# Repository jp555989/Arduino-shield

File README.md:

# Arduino-shield
This is a project I made for my engineer thesis which involves designing a shield for Arduino with as many useful functions as possible, using ready to program modules like LCD Display, RTC module, etc.

I used KiCad for designing the PCB and LtSpice for the simulation of electronic circuits, simulations involved op-amp in voltage phase inverting configuration, buffer and resistor ladder with Monte Carlo Method.

Presented files have updated version of PCB with important fixes, the board presented on photos is the older version.

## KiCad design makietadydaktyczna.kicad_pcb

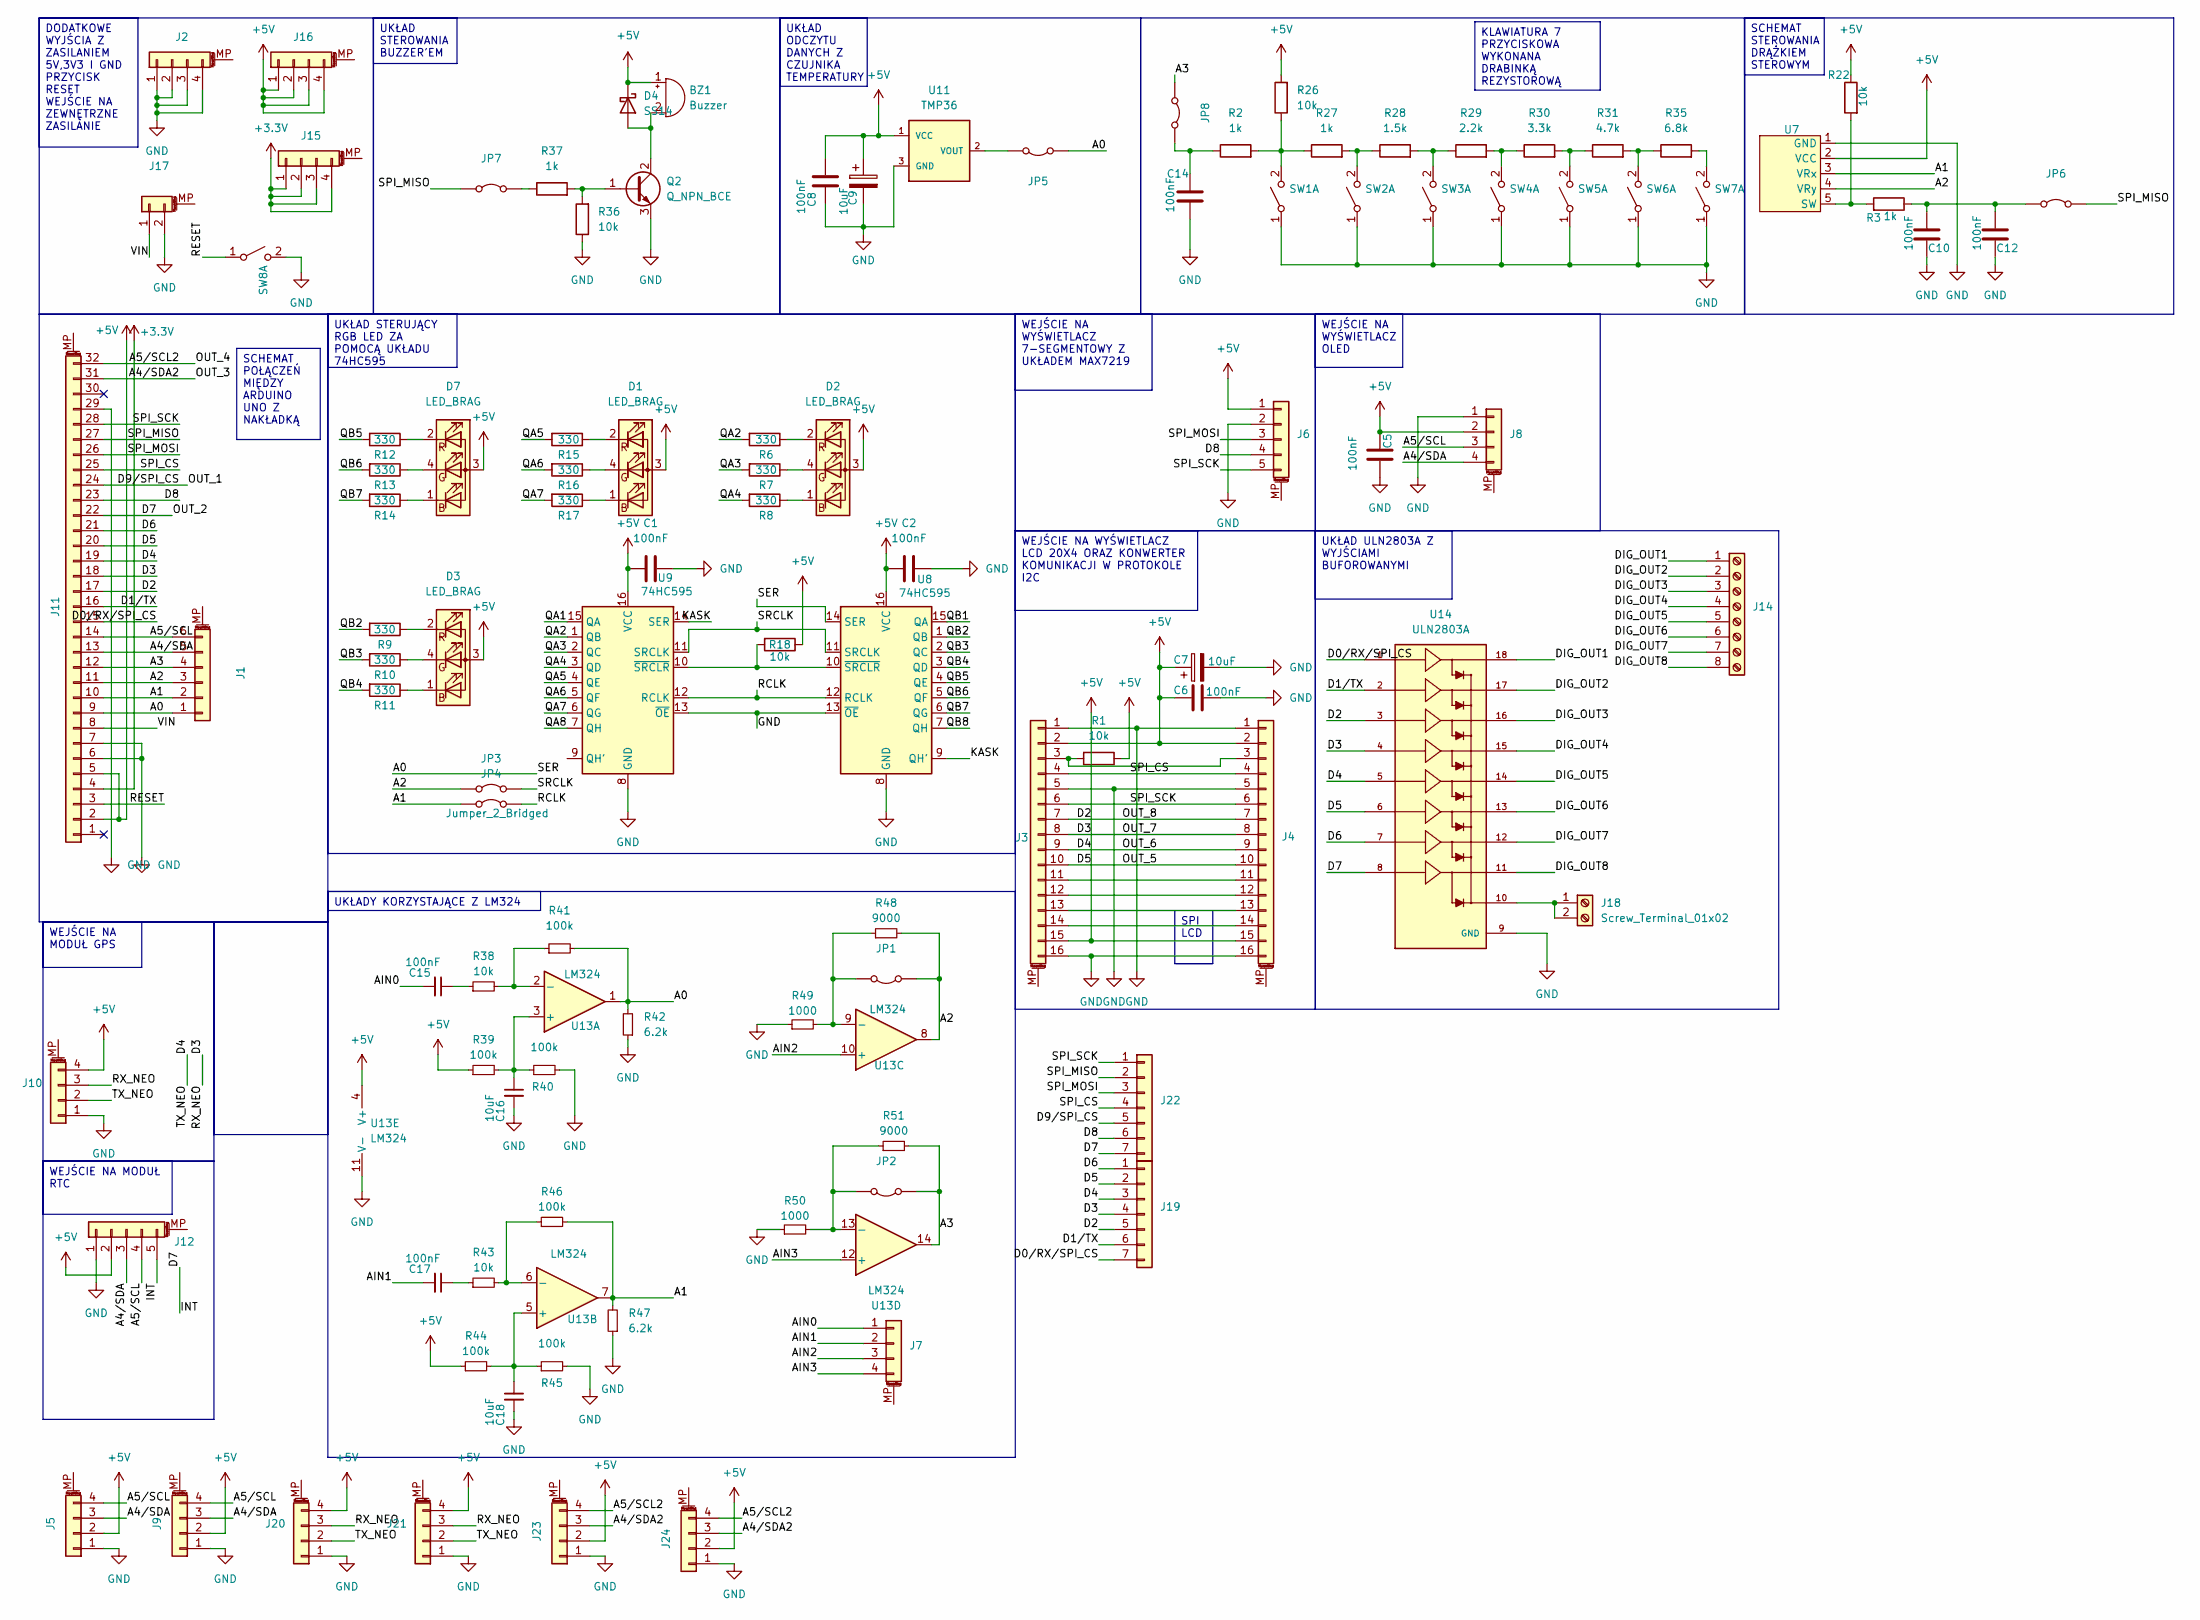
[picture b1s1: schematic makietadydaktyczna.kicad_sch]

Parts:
BZ1: Buzzer; Buzzer_D14mm_H7mm_P10mm
C1, C2, C5, C6, C8, C10, C12, C14, C15, C17: 100nF; C_0805_2012Metric_Pad1.18x1.45mm_HandSolder
C7, C9: 10uF; C_Radial_D5.0mm_H11.0mm_P2.00mm
C16, C18: 10uF; C_0805_2012Metric_Pad1.18x1.45mm_HandSolder
D1, D2, D3, D7: LED_BRAG; LED_D5.0mm-4_RGB_Wide_Pins
D4: SS14; D_SMA
J1: Conn_01x06_MountingPin; PinSocket_1x06_P2.54mm_Vertical
J2, J5, J8, J9, J10, J15, J16, J20, J21, J23, J24: Conn_01x04_MountingPin; PinSocket_1x04_P2.54mm_Vertical
J3, J4: Conn_01x16_MountingPin; PinSocket_1x16_P2.54mm_Vertical
J6, J12: Conn_01x05_MountingPin; PinSocket_1x05_P2.54mm_Vertical
J7: Conn_01x04_MountingPin; PinHeader_1x04_P2.54mm_Vertical
J11: Conn_01x32_MountingPin; Arduino_UNO_R3
J14: Screw_Terminal_01x08; TerminalBlock_Xinya_XY308-2.54-8P_1x08_P2.54mm_Horizontal
J17: Conn_01x02_MountingPin; PinSocket_1x02_P2.54mm_Vertical
J18: Screw_Terminal_01x02; TerminalBlock_Xinya_XY308-2.54-2P_1x02_P2.54mm_Horizontal
J19, J22: Conn_01x07; PinSocket_1x07_P2.54mm_Vertical
JP1, JP2, JP3, JP4, JP5, JP6, JP7, JP8: Jumper_2_Bridged; PinHeader_1x02_P2.54mm_Vertical
Q2: Q_NPN_BCE; TO-92
R1, R18, R22, R26, R36, R38, R43: 10k; R_0805_2012Metric_Pad1.20x1.40mm_HandSolder
R2, R3, R27, R37: 1k; R_0805_2012Metric_Pad1.20x1.40mm_HandSolder
R6, R7, R8, R9, R10, R11, R12, R13, R14, R15, R16, R17: 330; R_0805_2012Metric_Pad1.20x1.40mm_HandSolder
R28: 1.5k; R_0805_2012Metric_Pad1.20x1.40mm_HandSolder
R29: 2.2k; R_0805_2012Metric_Pad1.20x1.40mm_HandSolder
R30: 3.3k; R_0805_2012Metric_Pad1.20x1.40mm_HandSolder
R31: 4.7k; R_0805_2012Metric_Pad1.20x1.40mm_HandSolder
R35: 6.8k; R_0805_2012Metric_Pad1.20x1.40mm_HandSolder
R39, R40, R41, R44, R45, R46: 100k; R_0805_2012Metric_Pad1.20x1.40mm_HandSolder
R42, R47: 6.2k; R_0805_2012Metric_Pad1.20x1.40mm_HandSolder
R48, R51: 9000; R_0805_2012Metric_Pad1.20x1.40mm_HandSolder
R49, R50: 1000; R_0805_2012Metric_Pad1.20x1.40mm_HandSolder
SW1, SW2, SW3, SW4, SW5, SW6, SW7, SW8: SW_DPST_x2; SW_PUSH_6mm_H5mm
U6: (no value)
U7: PinSocket_1x05_P2.54mm_Vertical
U8, U9: 74HC595; SO16
U11: TMP36; TO-92
U13: LM324; SOIC127P600X175-14N
U14: ULN2803A; SOIC127P1030X265-18N; PARTREV 4

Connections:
+3.3V: J11.4, J15.1, J15.2, J15.3, J15.4
+5V: BZ1.1 (+), C1.1, C2.1, C5.2, C6.1, C7.1, C8.1, C9.1, D1.3 (A), D2.3 (A), D3.3 (A), D4.1 (K), D7.3 (A), J3.2, J3.15, J4.2, J4.15, J5.2, J6.1, J8.2, J9.2, J10.4, J11.2, J11.5, J12.2, J16.1, J16.2, J16.3, J16.4, J20.4, J21.4, J23.2, J24.2, R1.1, R18.1, R22.1, R26.2, R39.1, R44.1, U7.2 (VCC), U8.16 (VCC), U9.16 (VCC), U11.1 (VCC), U13.4 (V+)
/A0: J1.1, J11.9, JP5.1 (A), R41.2, R42.2, U8.14 (SER), U13.1
/A1: J1.2, J11.10, JP4.1 (A), R46.2, R47.2, U7.3 (VRx), U13.7
/A2: J1.3, J11.11, JP1.1 (A), JP3.1 (A), R48.2, U7.4 (VRy), U13.8
/A3: J1.4, J11.12, JP2.1 (A), JP8.1 (A), R51.2, U13.14
/A4/SDA: J1.5, J5.3, J8.4, J9.3, J11.13, J12.3
/A4/SDA2: J11.31, J23.3, J24.3
/A5/SCL: J1.6, J5.4, J8.3, J9.4, J11.14, J12.4
/A5/SCL2: J11.32, J23.4, J24.4
/AIN0: C15.2, J7.1
/AIN1: C17.2, J7.2
/AIN2: J7.3, U13.10 (+)
/AIN3: J7.4, U13.12 (+)
/D0/RX/SPI_CS: J11.15, J19.7, U14.1
/D1/TX: J11.16, J19.6, U14.2
/D2: J3.7, J4.7, J11.17, J19.5, U14.3
/D3: J3.8, J4.8, J10.3, J11.18, J19.4, J20.3, J21.3, U14.4
/D4: J3.9, J4.9, J10.2, J11.19, J19.3, J20.2, J21.2, U14.5
/D5: J3.10, J4.10, J11.20, J19.2, U14.6
/D6: J11.21, J19.1, U14.7
/D7: J11.22, J12.5, J22.7, U14.8
/D8: J6.4, J11.23, J22.6
/D9/SPI_CS: J11.24, J22.5
/DIG_OUT1: J14.1, U14.18
/DIG_OUT2: J14.2, U14.17
/DIG_OUT3: J14.3, U14.16
/DIG_OUT4: J14.4, U14.15
/DIG_OUT5: J14.5, U14.14
/DIG_OUT6: J14.6, U14.13
/DIG_OUT7: J14.7, U14.12
/DIG_OUT8: J14.8, U14.11
/KASK: U8.9 (QH'), U9.14 (SER)
/QA1: U9.15 (QA)
/QA2: R6.2, U9.1 (QB)
/QA3: R7.2, U9.2 (QC)
/QA4: R8.2, U9.3 (QD)
/QA5: R15.2, U9.4 (QE)
/QA6: R16.2, U9.5 (QF)
/QA7: R17.2, U9.6 (QG)
/QA8: U9.7 (QH)
/QB1: U8.15 (QA)
/QB2: R9.2, U8.1 (QB)
/QB3: R10.2, U8.2 (QC)
/QB4: R11.2, U8.3 (QD)
/QB5: R12.2, U8.4 (QE)
/QB6: R13.2, U8.5 (QF)
/QB7: R14.2, U8.6 (QG)
/QB8: U8.7 (QH)
/RCLK: JP4.2 (B), U8.12 (RCLK), U9.12 (RCLK)
/RESET: J11.3, SW8.1 (A); also elsewhere on the board
/SPI_CS: J3.4, J4.4, J11.25, J22.4
/SPI_MISO: J11.27, J22.2, JP6.2 (B), JP7.1 (A)
/SPI_MOSI: J6.3, J11.26, J22.3
/SPI_SCK: J3.6, J4.6, J6.5, J11.28, J22.1
/SRCLK: JP3.2 (B), U8.11 (SRCLK), U9.11 (SRCLK)
/VIN: J11.8, J17.1
GND: C1.2, C2.2, C5.1, C6.2, C7.2, C8.2, C9.2, C10.2, C12.2, C14.1, C16.2, C18.2, J2.1, J2.2, J2.3, J2.4, J3.1, J3.5, J3.16, J4.1, J4.5, J4.16, J5.1, J6.2, J8.1, J9.1, J10.1, J11.6, J11.7, J11.29, J12.1, J17.2, J20.1, J21.1, J23.1, J24.1, Q2.3 (E), R36.1, R40.2, R42.1, R45.2, R47.1, R49.1, R50.1, SW1.1 (A), SW2.1 (A), SW3.1 (A), SW4.1 (A), SW5.1 (A), SW6.1 (A), SW7.1 (A), SW8.2 (B), U7.1 (GND), U8.8 (GND), U8.13 (~OE), U9.8 (GND), U9.13 (~OE), U11.3 (GND), U13.11 (V-), U14.9 (GND); also elsewhere on the board
unnamed: BZ1.2 (-), D4.2 (A), Q2.2 (C)
unnamed: C15.1, R38.1
unnamed: C17.1, R43.1
unnamed: D1.1 (BK), R17.1
unnamed: D1.4 (GK), R16.1
unnamed: D1.2 (RK), R15.1
unnamed: D2.1 (BK), R8.1
unnamed: D2.4 (GK), R7.1
unnamed: D2.2 (RK), R6.1
unnamed: D3.1 (BK), R11.1
unnamed: D3.4 (GK), R10.1
unnamed: D3.2 (RK), R9.1
unnamed: D7.1 (BK), R14.1
unnamed: D7.4 (GK), R13.1
unnamed: D7.2 (RK), R12.1
unnamed: J3.3, J4.3, R1.2
unnamed: J3.11, J4.11
unnamed: J3.12, J4.12
unnamed: J3.13, J4.13
unnamed: J3.14, J4.14
unnamed: J18.1, J18.2, U14.10
unnamed: JP1.2 (B), R48.1, R49.2, U13.9 (-)
unnamed: JP2.2 (B), R50.2, R51.1, U13.13 (-)
unnamed: JP5.2 (B), U11.2 (VOUT)
unnamed: C10.1, C12.1, JP6.1 (A), R3.1
unnamed: JP7.2 (B), R37.1
unnamed: C14.2, JP8.2 (B), R2.1
unnamed: Q2.1 (B), R36.2, R37.2
unnamed: R2.2, R26.1, R27.1, SW1.2 (B)
unnamed: R27.2, R28.1, SW2.2 (B)
unnamed: R28.2, R29.1, SW3.2 (B)
unnamed: R29.2, R30.1, SW4.2 (B)
unnamed: R30.2, R31.1, SW5.2 (B)
unnamed: R31.2, R35.1, SW6.2 (B)
unnamed: R35.2, SW7.2 (B)
unnamed: R3.2, R22.2, U7.5 (SW)
unnamed: R18.2, U8.10 (~SRCLR), U9.10 (~SRCLR)
unnamed: C16.1, R39.2, R40.1, U13.3 (+)
unnamed: R38.2, R41.1, U13.2 (-)
unnamed: C18.1, R44.2, R45.1, U13.5 (+)
unnamed: R43.2, R46.1, U13.6 (-)

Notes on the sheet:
SCHEMAT STEROWANIA DRĄŻKIEM STEROWYM
KLAWIATURA 7 PRZYCISKOWA WYKONANA DRABINKĄ REZYSTOROWĄ
SCHEMAT POŁĄCZEŃ MIĘDZY ARDUINO UNO Z NAKŁADKĄ
WEJŚCIE NA MODUŁ RTC
DODATKOWE WYJŚCIA Z ZASILANIEM 5V,3V3 I GND PRZYCISK RESET WEJŚCIE NA ZEWNĘTRZNE ZASILANIE
WEJŚCIE NA MODUŁ GPS
UKŁADY KORZYSTAJĄCE Z LM324
SPI LCD
WEJŚCIE NA WYŚWIETLACZ 7-SEGMENTOWY Z UKŁADEM MAX7219
UKŁAD ODCZYTU DANYCH Z CZUJNIKA TEMPERATURY
UKŁAD ULN2803A Z WYJŚCIAMI BUFOROWANYMI
WEJŚCIE NA WYŚWIETLACZ LCD 20X4 ORAZ KONWERTER KOMUNIKACJI W PROTOKOLE I2C
UKŁAD STEROWANIA BUZZER'EM
WEJŚCIE NA WYŚWIETLACZ OLED
UKŁAD STERUJĄCY RGB LED ZA POMOCĄ UKŁADU 74HC595

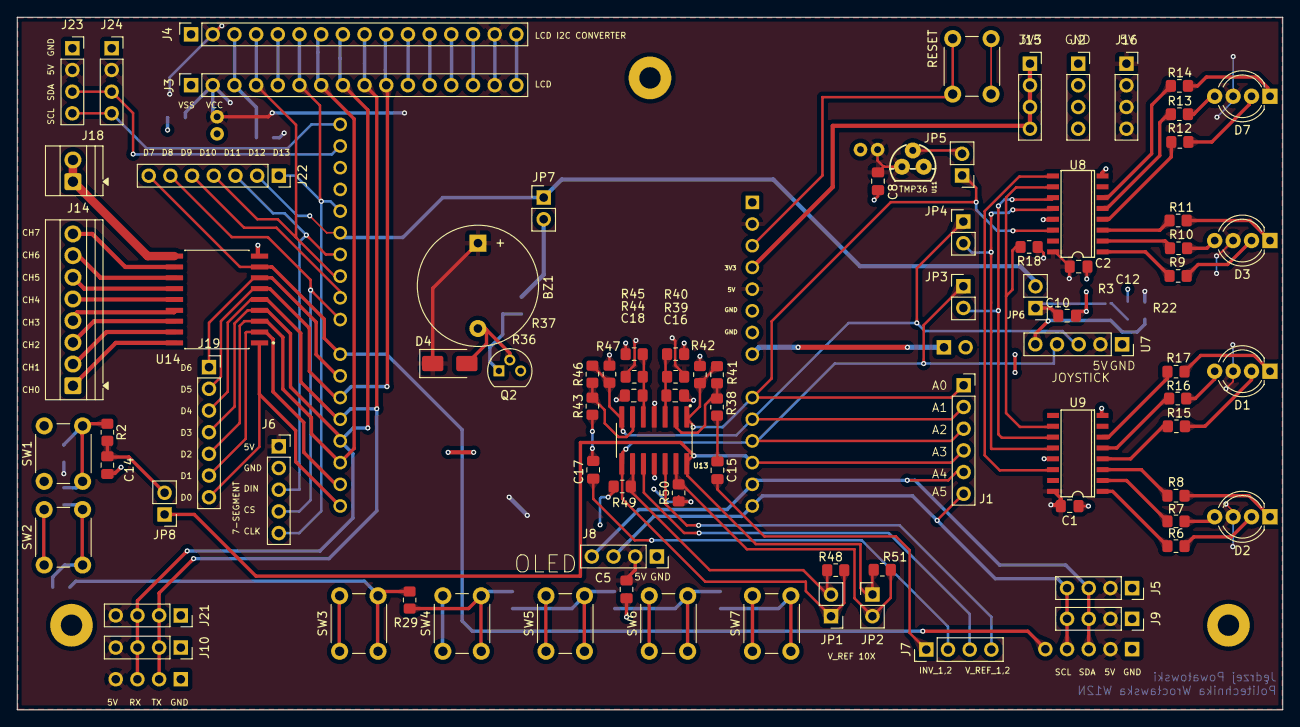
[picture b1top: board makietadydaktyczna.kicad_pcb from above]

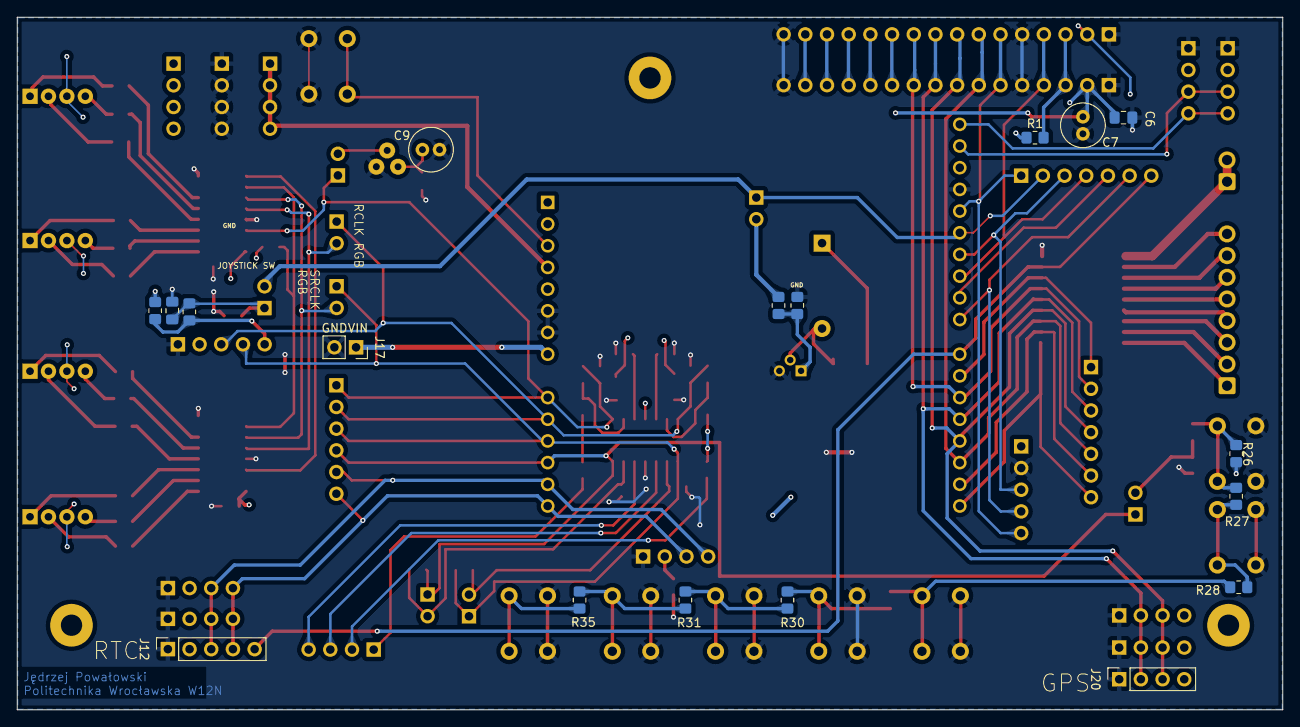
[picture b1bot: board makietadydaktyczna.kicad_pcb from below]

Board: 2 copper layers, 148.2 x 81.1 mm, 106 parts (18 on the bottom side), 95 nets.

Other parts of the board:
RESET: SW_DPST_x2; SW_PUSH_6mm_H5mm

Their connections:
/RESET: RESET.2 (B); also elsewhere on the board
GND: RESET.1 (A); also elsewhere on the board

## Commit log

2025-12-21 Enhance README with project details and images
    Expanded project description and added details about tools used for PCB design and circuit simulation.
2026-01-10 Updated design
    -Added multiplexed pins for communication protocols (I2C, UART)
    -Fixed problems with ULN2803A COM pin
    -Added multiplexed digital pins
    -Fixed opamp problems involving disconnected ground plane
    -Fixed problem with opamp reading voltage drop from resistor ladder from buttons
    -Increased the size of the board a little
2026-01-10 Update README with new PCB version and fixes
    Updated README to reflect the latest PCB version and fixes.
